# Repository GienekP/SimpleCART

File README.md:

# SimpleCART
Cartridge project for ATARI XE computers based on ATF22V10C

This bank-switched cartridge occupies 8 KB of address space between $A000 and $BFFF. The cartridge memory is divided into 16 banks, 8 KB each. The 4 lowest bits of the DATA written to $D500-$D50F (mirrored) select the bank mapped to $A000-$BFFF. Writing to $D510-$D51F disables the cartridge. The 2 lowest bits of the DATA written to $D520-$D52F (mirrored) select the "side" of SST39SF020A/SST39SF040"

SST39SF010A - 128kB

SST39SF020A - 256kB (2 sides)

SST39SF040 - 512kB (4 sides)

E.g.

POKE 54528,5 - select bank: 5

POKE 54560,1 - select side: 1

POKE 54544,0 - disable CART

The presented solution can be used unlimitedly and freely without any legal obligations, especially in the field of educational, commercial and non-commercial activities.

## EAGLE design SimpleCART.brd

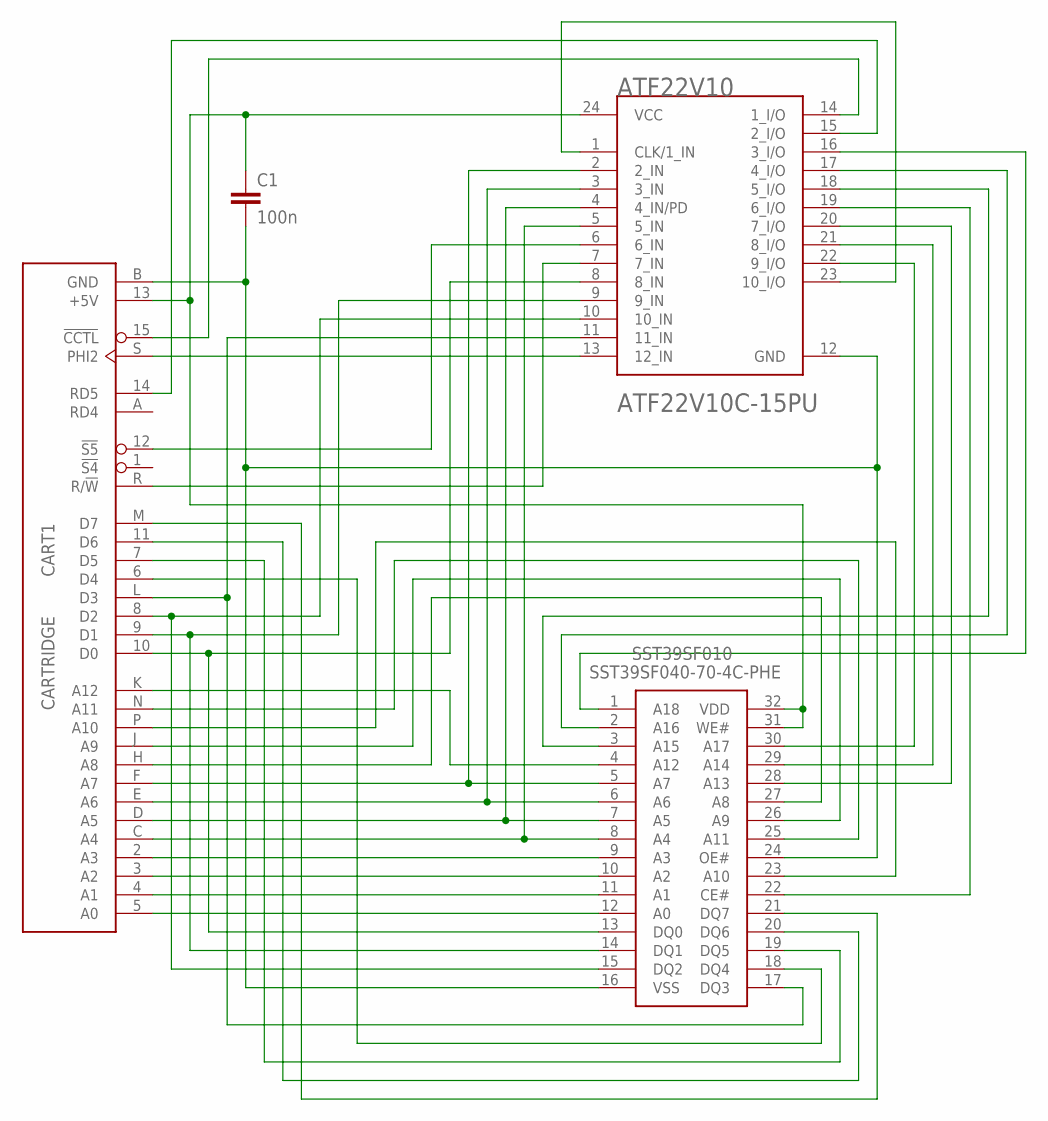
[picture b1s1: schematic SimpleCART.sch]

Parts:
ATF22V10: MICROCHIP_ATF22V10C-15PUMICROCHIP_ATF22V10C-15PU_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; MICROCHIP_ATF22V10C-15PU_0
C1: 100n; C025-024X044
CART1: CARTRIDGE
SST39SF010: SST39SF040-70-4C-PHE; DIP1556W56P254L4191H508Q32N

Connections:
A0: CART1.5 (A0), SST39SF010.12 (A0)
A1: CART1.4 (A1), SST39SF010.11 (A1)
A2: CART1.3 (A2), SST39SF010.10 (A2)
A3: CART1.2 (A3), SST39SF010.9 (A3)
A4: ATF22V10.5 (5_IN), CART1.C (A4), SST39SF010.8 (A4)
A5: ATF22V10.4 (4_IN/PD), CART1.D (A5), SST39SF010.7 (A5)
A6: ATF22V10.3 (3_IN), CART1.E (A6), SST39SF010.6 (A6)
A7: ATF22V10.2 (2_IN), CART1.F (A7), SST39SF010.5 (A7)
A8: CART1.H (A8), SST39SF010.27 (A8)
A9: CART1.J (A9), SST39SF010.26 (A9)
A10: CART1.P (A10), SST39SF010.23 (A10)
A11: CART1.N (A11), SST39SF010.25 (A11)
A12: CART1.K (A12), SST39SF010.4 (A12)
A13: ATF22V10.20 (7_I/O), SST39SF010.28 (A13)
A14: ATF22V10.21 (8_I/O), SST39SF010.29 (A14)
A15: ATF22V10.18 (5_I/O), SST39SF010.3 (A15)
A16: ATF22V10.17 (4_I/O), SST39SF010.2 (A16)
A17: ATF22V10.22 (9_I/O), SST39SF010.30 (A17)
A18: ATF22V10.16 (3_I/O), SST39SF010.1 (A18)
CCTL: ATF22V10.14 (1_I/O), CART1.15 (!CCTL)
CE: ATF22V10.19 (6_I/O), SST39SF010.22 (CE#)
CLK: ATF22V10.1 (CLK/1_IN), ATF22V10.23 (10_I/O)
D0: ATF22V10.8 (8_IN), CART1.10 (D0), SST39SF010.13 (DQ0)
D1: ATF22V10.9 (9_IN), CART1.9 (D1), SST39SF010.14 (DQ1)
D2: ATF22V10.10 (10_IN), CART1.8 (D2), SST39SF010.15 (DQ2)
D3: ATF22V10.11 (11_IN), CART1.L (D3), SST39SF010.17 (DQ3)
D4: CART1.6 (D4), SST39SF010.18 (DQ4)
D5: CART1.7 (D5), SST39SF010.19 (DQ5)
D6: CART1.11 (D6), SST39SF010.20 (DQ6)
D7: CART1.M (D7), SST39SF010.21 (DQ7)
GND: ATF22V10.12 (GND), C1.2, CART1.B (GND), SST39SF010.16 (VSS), SST39SF010.24 (OE#)
PHI2: ATF22V10.13 (12_IN), CART1.S (PHI2)
RD5: ATF22V10.15 (2_I/O), CART1.14 (RD5)
RW: ATF22V10.7 (7_IN), CART1.R (R/!W)
S5: ATF22V10.6 (6_IN), CART1.12 (!S5)
VCC: ATF22V10.24 (VCC), C1.1, CART1.13 (+5V), SST39SF010.31 (WE#), SST39SF010.32 (VDD)

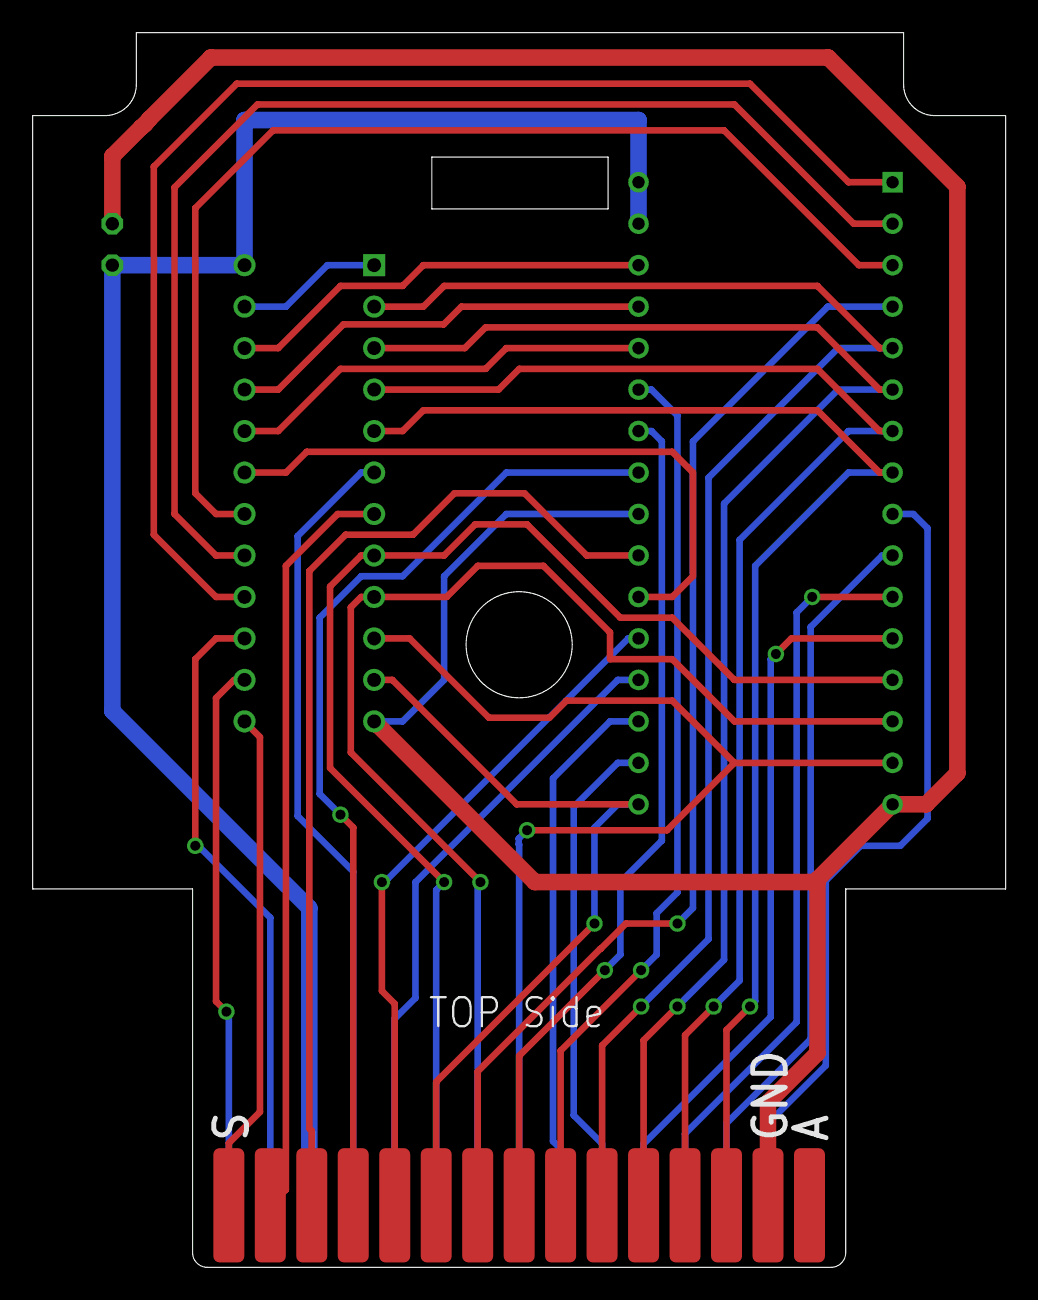
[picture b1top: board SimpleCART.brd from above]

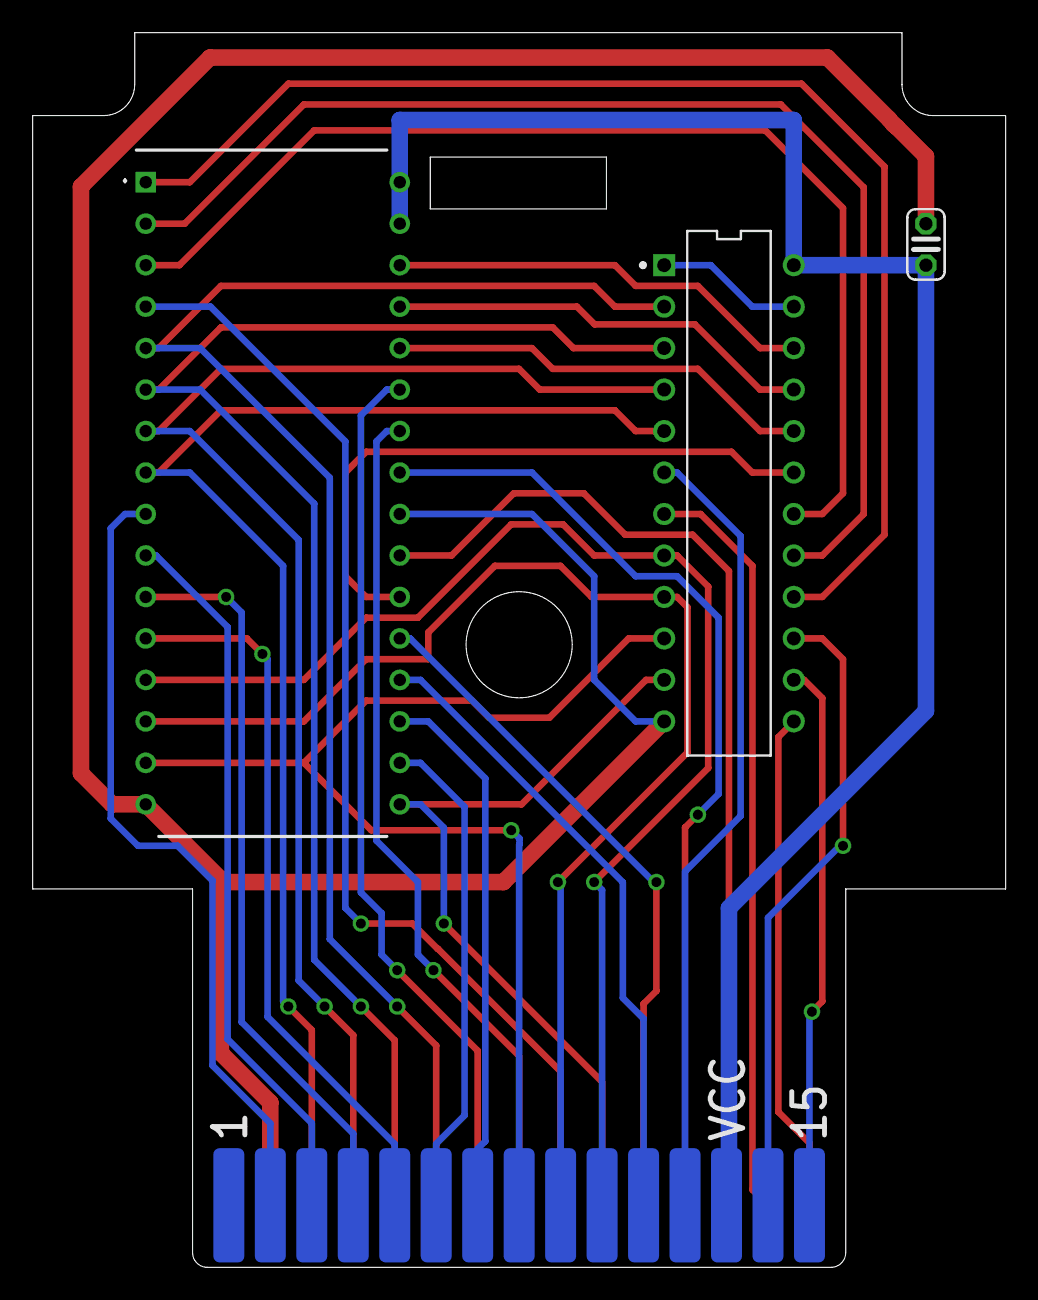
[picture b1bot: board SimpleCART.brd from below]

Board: 2 copper layers, 59.6 x 75.6 mm, 4 parts (4 on the bottom side), 36 nets.
